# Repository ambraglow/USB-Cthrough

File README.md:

# USB Cthrough

## Notes

- Pin headers are arranged in a way that this board can be plugged into a breadboard.
- Signal names are silkscreened on the board, top and bottom layers.
- This repository also includes files for manufacturing a 2x3 panel.
- I recommend a stencil for assembling this board.

## Info

- Software: Kicad 8
- Version: 3
- PCB size: 16.4mmx28mm
- Layer count: 6
- Recommended thickness: 0.8mm (for the USB-C plug)

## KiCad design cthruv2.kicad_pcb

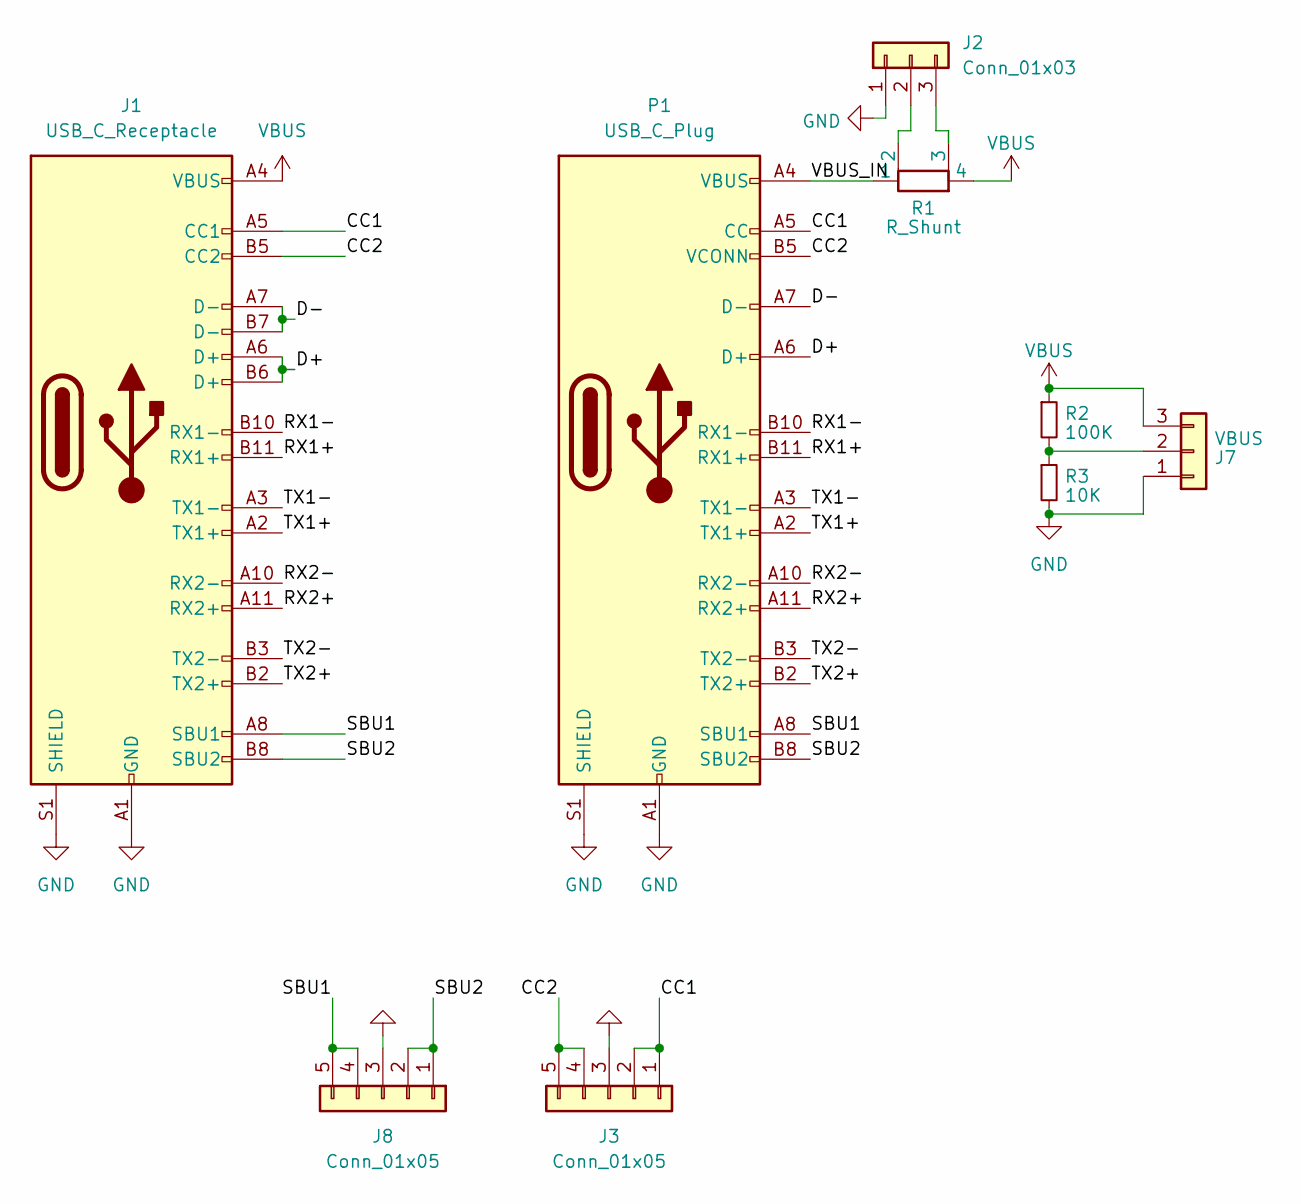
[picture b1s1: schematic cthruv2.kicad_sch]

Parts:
J1: USB_C_Receptacle; USB_C_Receptacle_Amphenol_12401548E4-2A; LCSC_ID C709359
J2: Conn_01x03; PinHeader_1x03_P2.54mm_Vertical
J3, J8: Conn_01x05; PinHeader_1x05_P2.54mm_Vertical
J7: VBUS; PinHeader_1x03_P2.54mm_Vertical
P1: USB_C_Plug; USB_C_Plug_Molex_105444; LCSC_ID C319150
R1: R_Shunt; Shunt; LCSC_ID C175856
R2: 100K; R_0603_1608Metric; LCSC_ID C25803
R3: 10K; R_0603_1608Metric; LCSC_ID C25804

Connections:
/CC1: J1.A5 (CC1), J3.1, J3.2, P1.A5 (CC)
/CC2: J1.B5 (CC2), J3.4, J3.5, P1.B5 (VCONN)
/D+: J1.A6 (D+), J1.B6 (D+), P1.A6 (D+)
/D-: J1.A7 (D-), J1.B7 (D-), P1.A7 (D-)
/RX1+: J1.B11 (RX1+), P1.B11 (RX1+)
/RX1-: J1.B10 (RX1-), P1.B10 (RX1-)
/RX2+: J1.A11 (RX2+), P1.A11 (RX2+)
/RX2-: J1.A10 (RX2-), P1.A10 (RX2-)
/SBU1: J1.A8 (SBU1), J8.4, J8.5, P1.A8 (SBU1)
/SBU2: J1.B8 (SBU2), J8.1, J8.2, P1.B8 (SBU2)
/TX1+: J1.A2 (TX1+), P1.A2 (TX1+)
/TX1-: J1.A3 (TX1-), P1.A3 (TX1-)
/TX2+: J1.B2 (TX2+), P1.B2 (TX2+)
/TX2-: J1.B3 (TX2-), P1.B3 (TX2-)
/VBUS_IN: P1.A4 (VBUS), P1.A9 (VBUS), P1.B4 (VBUS), P1.B9 (VBUS), R1.1
GND: J1.A1 (GND), J1.A12 (GND), J1.B1 (GND), J1.B12 (GND), J1.S1 (SHIELD), J2.1, J3.3, J7.1, J8.3, P1.A1 (GND), P1.A12 (GND), P1.B1 (GND), P1.B12 (GND), P1.S1 (SHIELD), R3.2
unnamed: J2.2, R1.2
unnamed: J2.3, R1.3
unnamed: J7.2, R2.2, R3.1
VBUS: J1.A4 (VBUS), J1.A9 (VBUS), J1.B4 (VBUS), J1.B9 (VBUS), J7.3, R1.4, R2.1

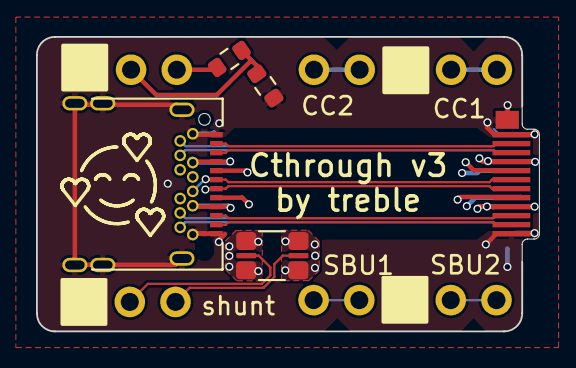
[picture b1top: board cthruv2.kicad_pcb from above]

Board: 6 copper layers, 27.9 x 16.4 mm, 9 parts (0 on the bottom side), 20 nets.

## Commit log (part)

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2025-03-31 Adding gitignore
2025-03-31 v3: rerouted pin header pinout, improved routing
2025-03-31 panel json file: JLCPCB, 2x3, extended PCBA (=> >70x70 size panel)
2025-03-31 small insignificant fix (two unused keepouts removed from outside the board area)
2025-03-31 adding README template
2025-03-31 adding plugin-generated files to gitignore
